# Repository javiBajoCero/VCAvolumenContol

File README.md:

# VCAvolumenContol
## Table of contents
* [General info](#general-info)
* [Technologies](#technologies)
* [Setup](#setup)
* [Datasheets](#datasheets)

## General info
This is a Voltage Controled Volume control based on the LM13700 IC, dual transconductance amplifiers with builtin output buffers. \
Why not just a potentiometer? \
Because i dont want the precious audio signal rerouted trough god knows where 1 or 2 meters catching up all kind of noise. \
Controlling the op amp transductance with a (filtered) external dc voltage/current sounds like the best approach, and makes the board modular friendly!
	
## Technologies
Project is created with:
* Eagle
	
## Setup
Just open it with eagle

```
:D
```

## Datasheets
https://www.ti.com/lit/ds/symlink/lm13700.pdf

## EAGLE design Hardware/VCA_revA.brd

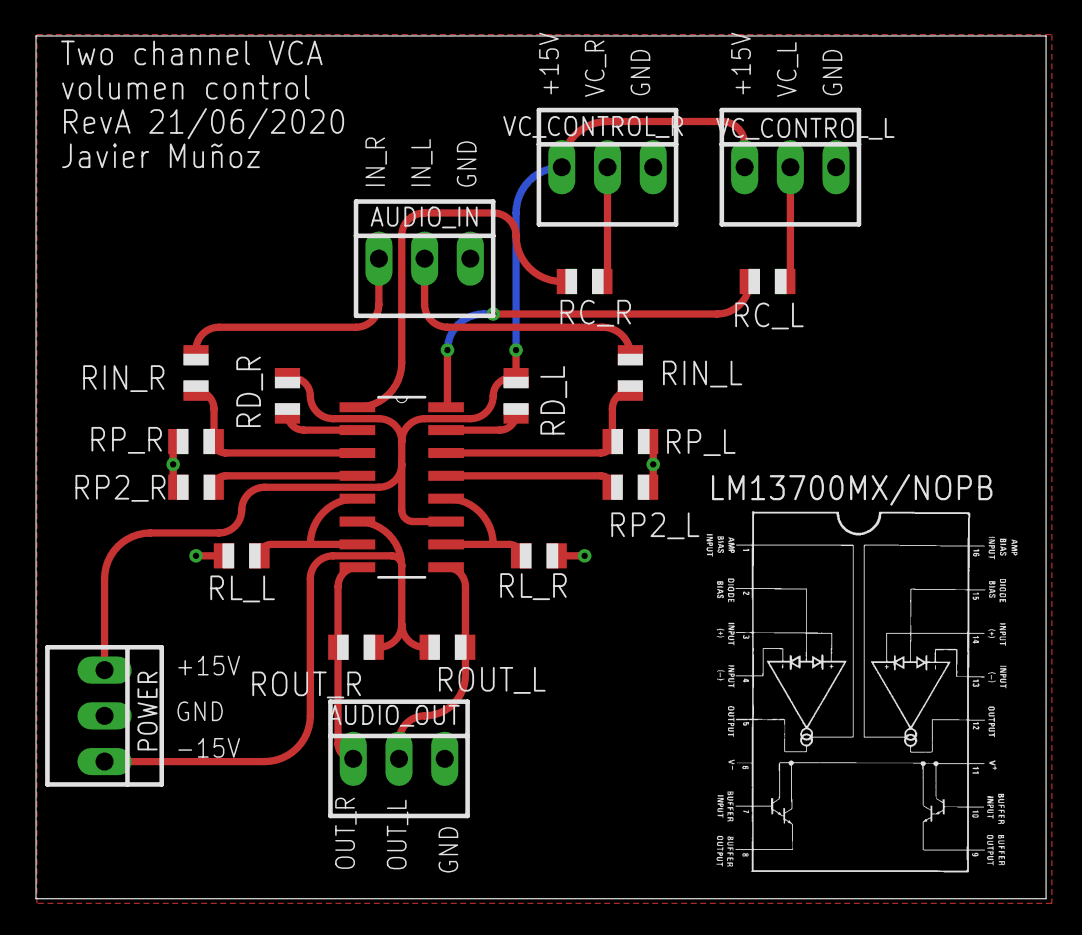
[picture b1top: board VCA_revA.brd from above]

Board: 2 copper layers, 56.1 x 47.9 mm, 20 parts (0 on the bottom side), 19 nets.

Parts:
AUDIO_IN: 22-23-2031
AUDIO_OUT: 22-23-2031
LM13700MX/NOPB: LM13700MX/NOPB; SOIC127P620X175-16N
POWER: 22-23-2031
RC_L: 30K; R0805
RC_R: 30K; R0805
RD_L: 15K; R0805
RD_R: 15K; R0805
RIN_L: 10K; R0805
RIN_R: 10K; R0805
RL_L: 10k; R0805
RL_R: 10k; R0805
ROUT_L: 5,1k; R0805
ROUT_R: 5,1k; R0805
RP2_L, RP2_R: 510; R0805
RP_L: 510; R0805
RP_R: 510; R0805
VC_CONTROL_L: 22-23-2031
VC_CONTROL_R: 22-23-2031

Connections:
-15V: LM13700MX/NOPB.6, POWER.3, ROUT_L.1, ROUT_R.1
AMP_BIAS_IN: LM13700MX/NOPB.16, RC_L.1
AMP_BIAS_IN_2: LM13700MX/NOPB.1, RC_R.1
AUDIO_L: AUDIO_IN.2, RIN_L.1
AUDIO_L+: LM13700MX/NOPB.14, RIN_L.2, RP_L.2
AUDIO_L-: LM13700MX/NOPB.13, RP2_L.1
AUDIO_R: AUDIO_IN.1, RIN_R.1
AUDIO_R+: LM13700MX/NOPB.3, RIN_R.2, RP_R.2
AUDIO_R-: LM13700MX/NOPB.4, RP2_R.1
DIODE_BIAS: LM13700MX/NOPB.15, RD_L.2
DIODE_BIAS_2: LM13700MX/NOPB.2, RD_R.2
GND: AUDIO_IN.3, AUDIO_OUT.3, POWER.2, RL_L.1, RL_R.1, RP2_L.2, RP2_R.2, RP_L.1, RP_R.1, VC_CONTROL_L.3, VC_CONTROL_R.3
OPAMP_OUT_1: LM13700MX/NOPB.5, LM13700MX/NOPB.7, RL_L.2
OPAMP_OUT_2: LM13700MX/NOPB.10, LM13700MX/NOPB.12, RL_R.2
OUT_L: AUDIO_OUT.2, LM13700MX/NOPB.9, ROUT_L.2
OUT_R: AUDIO_OUT.1, LM13700MX/NOPB.8, ROUT_R.2
VCC: LM13700MX/NOPB.11, POWER.1, RD_L.1, RD_R.1, VC_CONTROL_L.1, VC_CONTROL_R.1
VC_CONTROL_L: RC_L.2, VC_CONTROL_L.2
VC_CONTROL_R: RC_R.2, VC_CONTROL_R.2

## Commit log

2020-09-20 revA of the board, simple smd 0804 dev board for testing LM13700 capabilities
2020-10-12 first eurorack shapped pcb for testing fittings, silkscreen and overall production quality check, this board doesnt mean to be functional, this is still under heavy development stage
2020-12-20 Bug in the pcb fixed, +12V rail was not connected in both VC in potentiometers. Also i added names to the chip rails
